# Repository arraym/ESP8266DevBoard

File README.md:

# **ESP8266DevBoard v1.1**

## Programming interface

The Serial UART interface is available at `J5` with the following pinout:

| Board Pin# | Signal | Required |
| ---------- | ------ | -------- |
| 1          | DTR    | YES      |
| 2          | RX     | YES      |
| 3          | TX     | YES      |
| 4          | RTS    | YES      |
| 5          | GND    | YES      |

For programming, all the pins marked as required must be connected.

**Remember to connect RX signal of the board to the RX signal of the programmer (same for TX).**

## Changelog

### **Changelog v1.1** ##
* J2, J3 (China RJ11 connectors) changed with RJ45 (MTJ-881X1)
* new LED and buzzer 12V controll lines added on each RJ45 connector

### **Changelog v1.2** ##
* J5 programming connector added (68001-420HLF)
* U2, Y1, C4, C5, C6, C7, D1, J1 set to DNP

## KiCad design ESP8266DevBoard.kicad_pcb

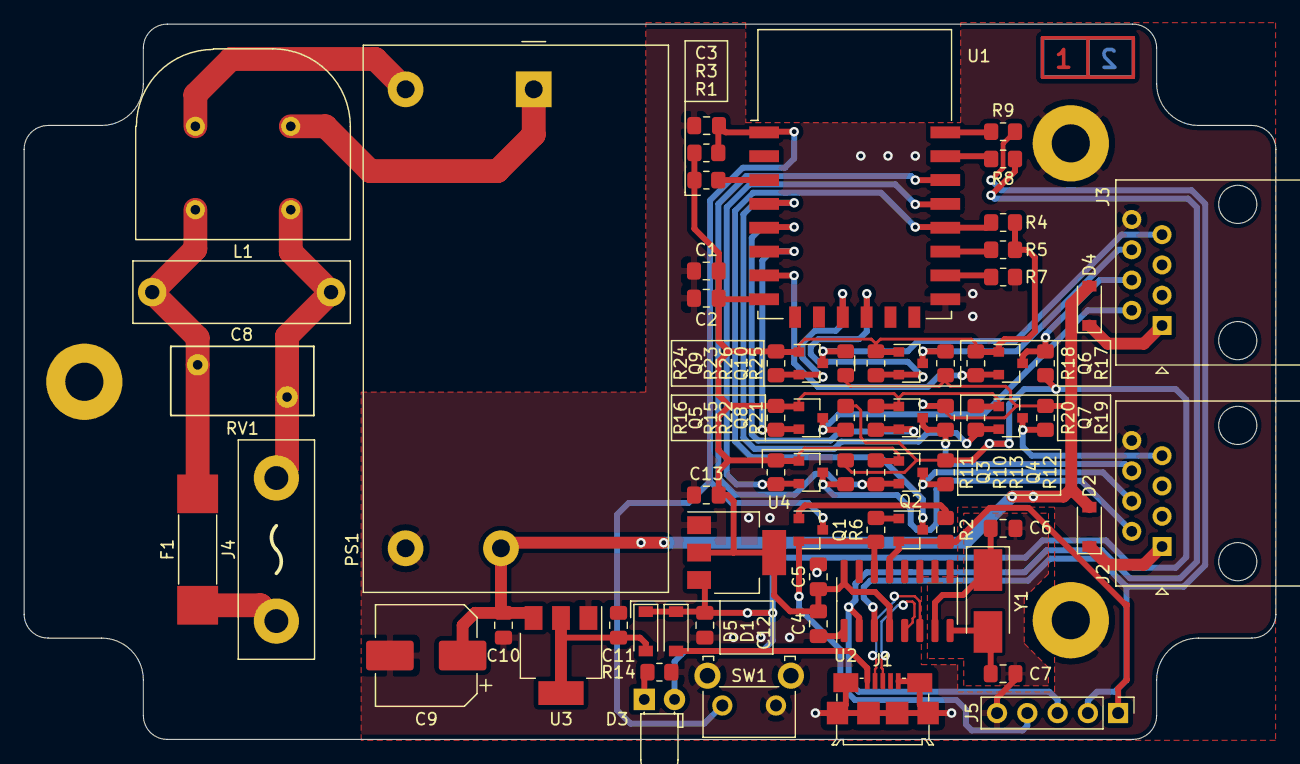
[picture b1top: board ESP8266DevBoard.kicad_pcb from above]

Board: 2 copper layers, 105.0 x 60.0 mm, 72 parts (0 on the bottom side), 47 nets.

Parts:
C1, C11, C13: 10u; C_0805_2012Metric_Pad1.18x1.45mm_HandSolder
C2, C3, C10, C12: 100n; C_0805_2012Metric_Pad1.18x1.45mm_HandSolder
C4: 100n, DNP; C_0805_2012Metric_Pad1.18x1.45mm_HandSolder
C5: 10u, DNP; C_0805_2012Metric_Pad1.18x1.45mm_HandSolder
C6, C7: 18p, DNP; C_0805_2012Metric_Pad1.18x1.45mm_HandSolder
C8: R46KI310000M1K1; C_Rect_L18.0mm_W5.0mm_P15.00mm_FKS3_FKP3
C9: 865080349013; CP_Elec_8x5.4
D1: 1N5819HWQ-7-F, DNP; D_SOD-123
D2, D4, D5: 1N5819HWQ-7-F; D_SOD-123
D3: PWR; LED_D3.0mm_Horizontal_O1.27mm_Z2.0mm
F1: 3405.0163.11; Fuse_10x3mm
H1, H2, H3: MH; MountingHole_3.2mm_M3_Pad
J1: 10118192-0001LF, DNP; USB_Micro-B_Amphenol_10118192-0001LF_Horizontal
J2, J3: MTJ-881X1; RJ45_Multicomp_MTJ-881X1_Horizontal
J4: AC; AC_Connector_2x2mm_P12mm
J5: 68001-420HLF; PinHeader_1x05_P2.54mm_Vertical
L1: SU9H-01100; L_SU9H
PS1: IRM-10-12; Converter_ACDC_MeanWell_IRM-10-xx_THT
Q1, Q2: BC847BLT1G; SOT-23
Q3, Q4, Q5, Q6, Q7, Q8, Q9, Q10: 2N7002H6327XTSA2; SOT-23
R1, R2, R3, R4, R5, R6, R7, R10, R11, R12, R13, R15, R16, R17, R18, R19, R20, R21, R22, R23, R24, R25, R26: 10k; R_0805_2012Metric_Pad1.20x1.40mm_HandSolder
R8, R9, R14: 470R; R_0805_2012Metric_Pad1.20x1.40mm_HandSolder
RV1: MOV-10D561K; RV_Disc_D12mm_W5.8mm_P7.5mm
SW1: B3F-3152; SW_Tactile_SKHH_Angled
U1: ESP-12F; ESP-12E
U2: CH340G, DNP; SOIC-16_3.9x9.9mm_P1.27mm
U3: LD1117S50TR; SOT-223-3_TabPin2
U4: LD1117S33TR; SOT-223-3_TabPin2
Y1: ABM3-12.000MHZ-D2Y-T, DNP; Crystal_SMD_5032-2Pin_5.0x3.2mm_HandSoldering

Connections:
+3V3: C1.2, C2.1, C4.1, C5.1, C13.1, Q3.1, Q4.1, Q5.1, Q6.1, Q7.1, Q8.1, Q9.1, Q10.1, R1.1, R3.1, R4.1, R5.1, R11.1, R13.1, R16.1, R18.1, R20.1, R22.1, R24.1, R26.1, U1.8, U2.4, U2.16, U4.2
+5V: C12.1, D1.1, D3.2, D5.1, R10.1, R12.1, R15.1, R17.1, U4.3
+12V: C9.1, C10.1, D2.2, D4.2, PS1.4, R19.1, R21.1, R23.1, R25.1, U3.3
BUZZ_1: Q8.2, R22.2, U1.5
BUZZ_2: Q10.2, R26.2, U1.12
DATA0_1: Q3.2, R11.2, U1.19
DATA0_2: Q5.2, R16.2, U1.6
DATA1_1: Q4.2, R13.2, U1.20
DATA1_2: Q6.2, R18.2, U1.7
DTR: J5.1, Q2.2, R2.1, U2.13
D_N: J1.2, U2.6
D_P: J1.3, U2.5
EN: R1.2, U1.3
GND: C1.1, C2.2, C3.2, C4.2, C5.2, C6.2, C7.2, C9.2, C10.2, C11.2, C12.2, C13.2, H2.1, H3.1, J1.5, J1.6, J2.8, J3.8, J5.5, PS1.3, R7.1, R14.2, SW1.1, SW1.3, SW1.4, U1.15, U2.1, U3.1, U4.1
GPIO0: Q2.3, R4.2, U1.18
GPIO2: R5.2, U1.17
GPIO15: R7.2, U1.16
LED_1: Q7.2, R20.2, U1.4
LED_2: Q9.2, R24.2, U1.11
unnamed: C6.1, U2.7, Y1.1
unnamed: C7.1, U2.8, Y1.2
unnamed: C8.1, F1.1, L1.3, RV1.1
unnamed: C8.2, J4.2, L1.1, RV1.2
unnamed: C11.1, D5.2, U3.2
unnamed: D1.2, J1.1
unnamed: D2.1, J2.1
unnamed: D3.1, R14.1
unnamed: D4.1, J3.1
unnamed: F1.2, J4.1
unnamed: J2.2, Q3.3, R10.2
unnamed: J2.4, Q4.3, R12.2
unnamed: J2.6, Q8.3, R21.2
unnamed: J2.7, Q7.3, R19.2
unnamed: J3.2, Q5.3, R15.2
unnamed: J3.4, Q6.3, R17.2
unnamed: J3.6, Q10.3, R25.2
unnamed: J3.7, Q9.3, R23.2
unnamed: L1.2, PS1.1
unnamed: L1.4, PS1.2
unnamed: Q1.1, R2.2
unnamed: Q2.1, R6.2
RST: C3.1, Q1.3, R3.2, SW1.2, U1.1
RTS: J5.4, Q1.2, R6.1, U2.14
RX: J5.2, R9.1, U2.3
RXD: R8.2, U1.21
TX: J5.3, R8.1, U2.2
TXD: R9.2, U1.22

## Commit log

2021-08-03 Initial commit.
2021-08-04 5V LDO added, second level shifter, board outline done.
2021-08-06 3mm LED added to schematic, footprints assigned.
2021-08-07 Components placed on the board.
2021-08-07 Routing done.
2021-08-08 PCB routing done, gerber files added.
2021-08-10 Mouser components basket added.
2021-09-19 Board corners fixed to match plastic case, all corners counded.
2021-09-24 RJ connectors changed, LED and buzzer controll lines added for each conector, readme file with rev changes added.
2021-09-27 Routing done, gerber files added (v1.1).
2022-09-19 Programming connector added, gerber files generated (v1.2).
2022-10-01 DNP components removed from paste file, programming connector silk added, paste and silk gerbers regenerated, new ibom file generated.
2022-10-03 README.md: updated with UART pinout
